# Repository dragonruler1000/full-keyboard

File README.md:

# full-keyboard
This is a 108 key keyboard that follows the ansi 104 key layout with 4 extra keys above the numpad. It has spots for two rotary encoders and a oled but to start i am going to not include those to reduce cost.

I wanted to make this to allow me to try a mechanical keyboard without needing to spend $200+ for a lowend mechanical keyboard and to give a chance to use QMK firmware.

To make this keyboard for your self upload the gerbers in [/PCB](/PCB) to your prefered pcb site. the case is split into 2 parts the files are in [/CAD](/CAD). firmware is built like any qmk firmware. instructions are in the folder as well. other parts are listed below and in BOM.csv and BOM.ods

Fully soldered keyboard (just need to get the case and keycaps).

BOM:
| Item Count | item name                    | Unit price $ | Total Price* | Price with discounts* | Link                                                            | Running total $* | Running total with coupons*    | part number | Notes                                                             |
|------------|------------------------------|--------------|--------------|-----------------------|-----------------------------------------------------------------|------------------|--------------------------------|-------------|-------------------------------------------------------------------|
| 1          | Raspi pico                   | 5            | 5            | 5                     | https://www.adafruit.com/product/5525                           | 5.3              | 5.3                            | 1           |                                                                   |
| 110        | 1N4148-t50A diode            | 0.0307       | 3.38         | 3.38                  | https://www.lcsc.com/product-detail/C895215.html                | 8.88             | 8.88                           | 2           | packs of 10                                                       |
| 108        | keycaps                      | 0            | 0            | 0                     | https://www.printables.com/model/118708-simple-cherry-mx-keycap | 8.88             | 8.88                           | 3           | 1g each can print myself                                          |
| 1          | Outemu(Gaote) Blue Switches  | 21.99        | 21.99        | 21.99                 | https://www.amazon.com/gp/product/B0CBSL2Z75                    | 32.19            | 32.19                          | 4           | pack of 108 price                                                 |
| 1          | DUROCK PCB mount stabalizers | 17.99        | 17.99        | 17.99                 | https://www.amazon.com/gp/product/B0B2RVN19F?psc=1              | 51.26            | 51.26                          | 5           | full set                                                          |
| 1          | heatset inserts              | 8.99         | 8.99         | 8.99                  | https://www.amazon.com/gp/product/B0CS6XJSSL                    | 60.79            | 60.79                          | 6           |                                                                   |
| 1          | PCB                          | 35.3         | 35.3         | 35.3                  | https://www.jlcpcb.com                                          | 98.21            | 98.21                          | 7           | jlcpcb price is cheaper then pcbway before shipping               |
| 1          | case                         | 0            | 0            | 0                     | N/A                                                             | 98.21            | 98.21                          | 8           | print using printing legion                                       |
| 1          | Shipping for PCB             | 41.4         | 41.4         | 22.16                 | N/A                                                             | 142.09           | 121.7                          |             | First shipping cost is for DHL express second one is for GDL      |
| 1          | digikey shipping and tarrifs | 5.36         | 5.36         | 5.36                  | N/A                                                             | 147.77           | 127.38                         |             | ±$5                                                               |
| 1          | Adafruit shipping            | 5.72         | 5.72         | 5.72                  | N/A                                                             | 153.83           | 133.44                         |             |                                                                   |
| 1          | amazon shipping              | 0            | 0            | 0                     | N/A                                                             | 153.83           | 133.44                         |             | over min amount for free shipping/have a 30 trial of amazon prime |
|            |                              |              |              |                       |                                                                 |                  |                                |             |                                                                   |
|            |                              |              |              |                       |                                                                 |                  | *Rounded to two decimal places |             |                                                                   |

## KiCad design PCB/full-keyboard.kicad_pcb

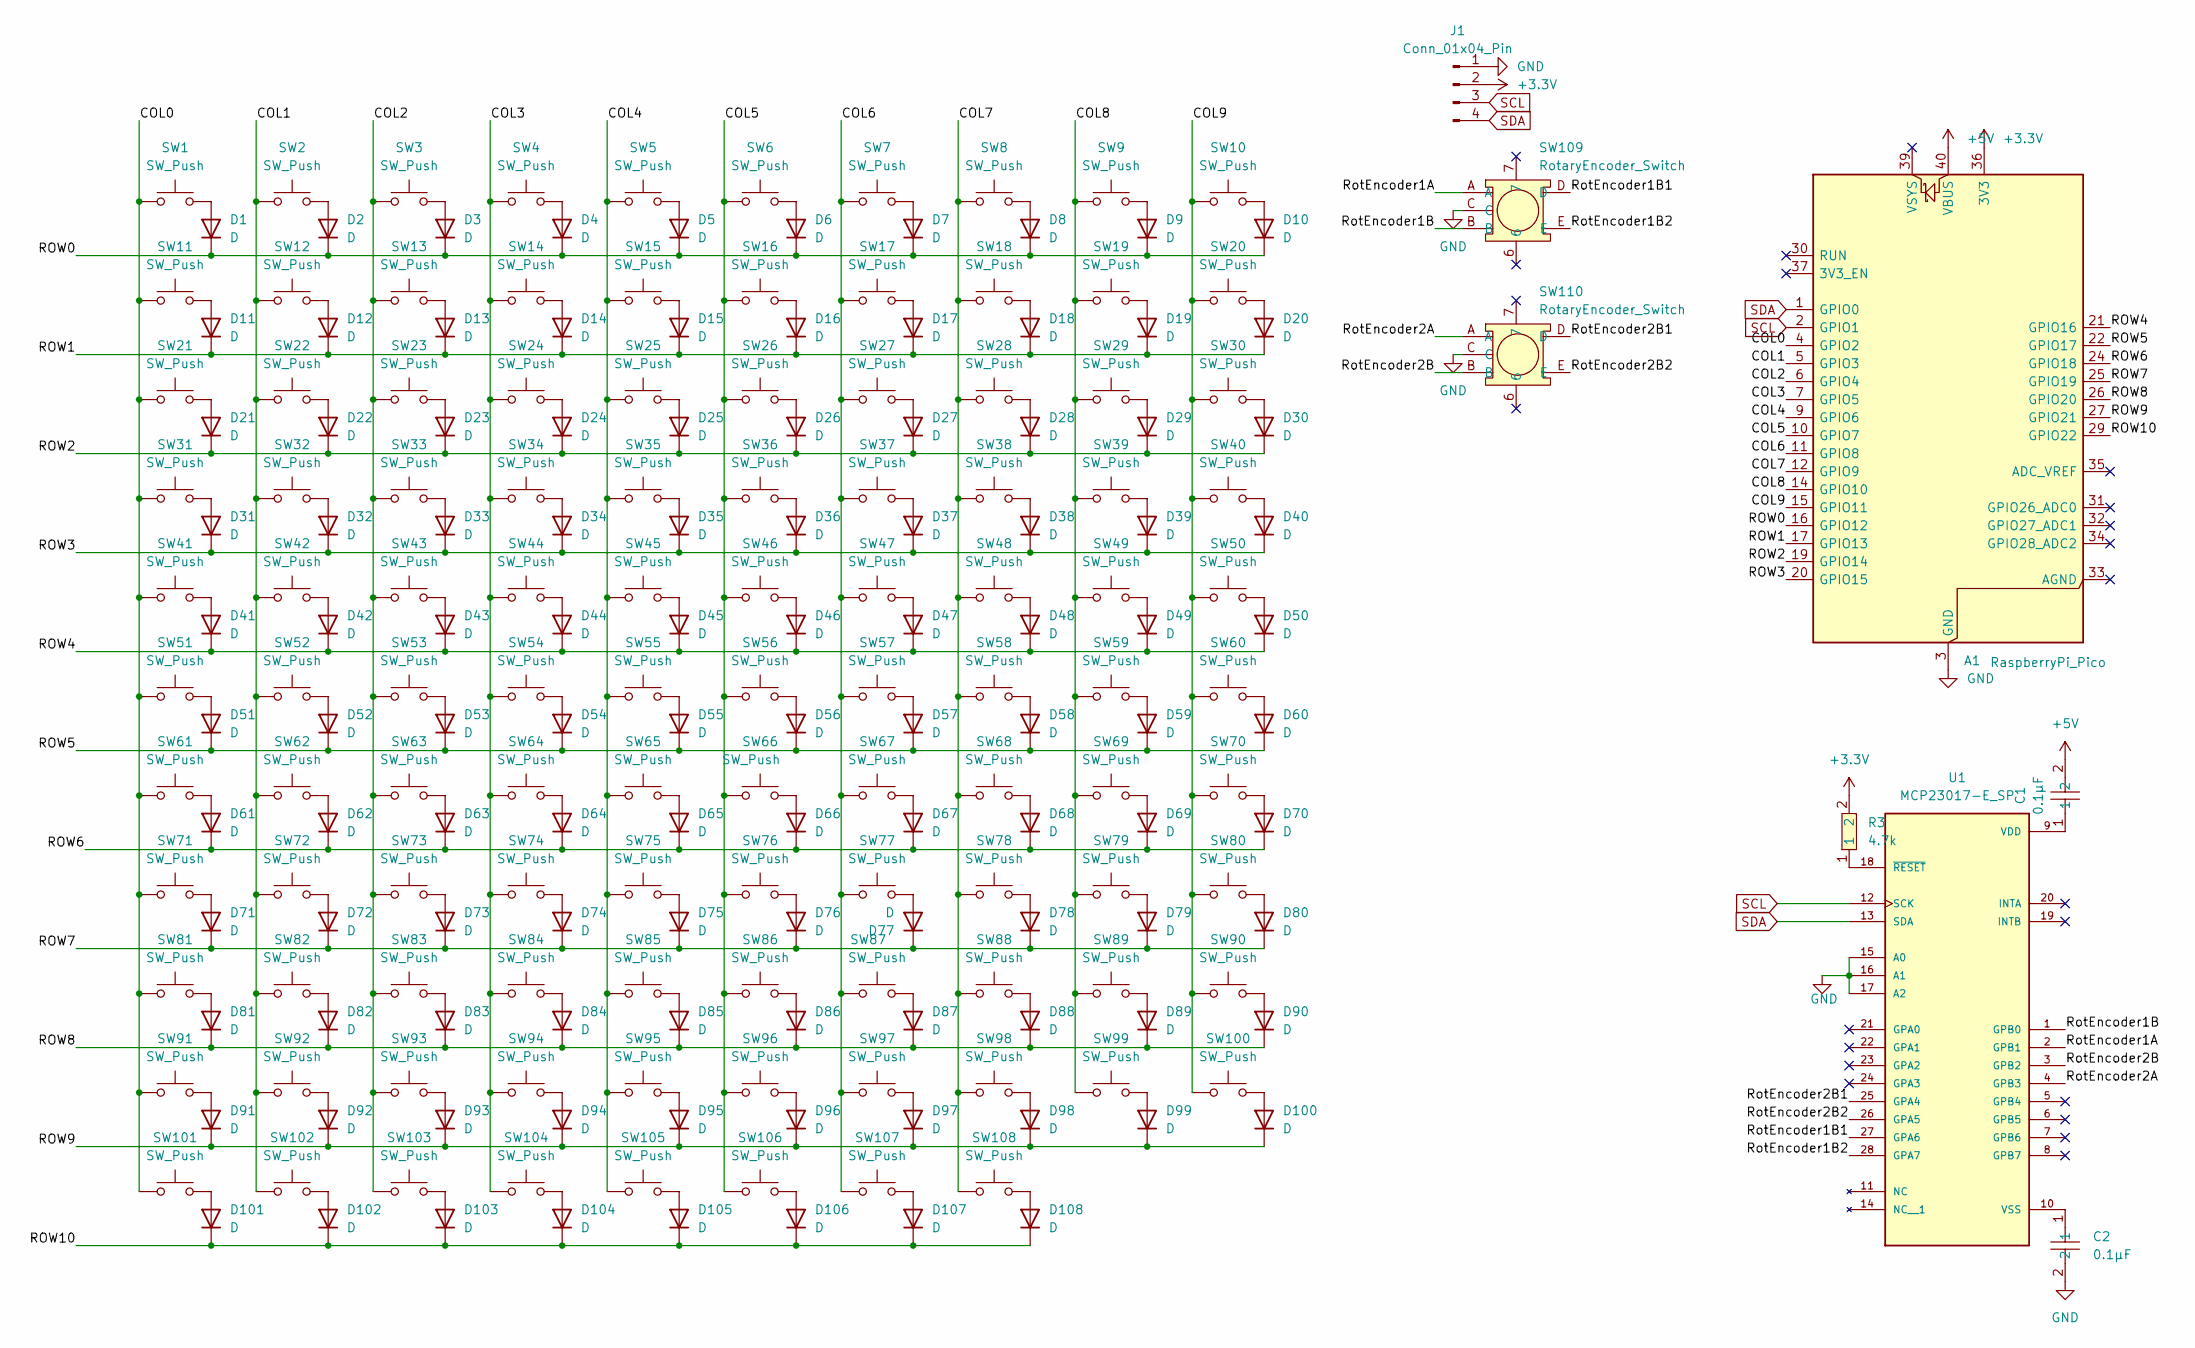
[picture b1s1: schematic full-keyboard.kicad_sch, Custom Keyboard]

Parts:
A1: RaspberryPi_Pico; RaspberryPi_Pico_Common_THT
C1, C2: 0.1µF; CAP-TH_L5.1-W3.2-P5.08-D0.50; LCSC Part C1622885
D1, D2, D3, D4, D5, D6, D7, D8, D9, D10, D11, D12, D13, D14, D15, D16, D17, D18, D19, D20, D21, D22, D23, D24, D25, D26, D27, D28, D29, D30, D31, D32, D33, D34, D35, D36, D37, D38, D39, D40, D41, D42, D43, D44, D45, D46, D47, D48, D49, D50, D51, D52, D53, D54, D55, D56, D57, D58, D59, D60, D61, D62, D63, D64, D65, D66, D67, D68, D69, D70, D71, D72, D73, D74, D75, D76, D77, D78, D79, D80, D81, D82, D83, D84, D85, D86, D87, D88, D89, D90, D91, D92, D93, D94, D95, D96, D97, D98, D99, D100, D101, D102, D103, D104, D105, D106, D107, D108: D; D_DO-35_SOD27_P7.62mm_Horizontal
J1: Conn_01x04_Pin; SSD1306-0.91-OLED-4pin-128x32
R3: 4.7k; RES-TH_BD2.5-L4.7-P8.70-D0.5; LCSC Part C172560
SW1, SW2, SW3, SW4, SW5, SW6, SW7, SW8, SW9, SW10, SW11, SW12, SW13, SW14, SW15, SW16, SW17, SW18, SW19, SW20, SW21, SW22, SW23, SW24, SW25, SW26, SW27, SW28, SW29, SW30, SW31, SW32, SW33, SW35, SW36, SW37, SW38, SW39, SW40, SW41, SW43, SW44, SW45, SW46, SW47, SW48, SW49, SW50, SW51, SW52, SW53, SW54, SW56, SW57, SW58, SW59, SW60, SW61, SW64, SW65, SW66, SW67, SW68, SW69, SW70, SW71, SW72, SW73, SW74, SW76, SW77, SW78, SW80, SW81, SW82, SW83, SW84, SW85, SW86, SW87, SW88, SW89, SW91, SW92, SW93, SW94, SW104, SW105, SW106, SW108: SW_Push; SW_Hotswap_Kailh_MX_1.00u
SW34, SW107: SW_Push; SW_Hotswap_Kailh_MX_2.00u
SW42, SW55: SW_Push; SW_Hotswap_Kailh_MX_1.50u
SW62, SW95: SW_Push; SW_Hotswap_Kailh_MX_2.00u_90deg
SW63: SW_Push; SW_Hotswap_Kailh_MX_1.75u
SW75, SW79: SW_Push; SW_Hotswap_Kailh_MX_2.25u
SW90: SW_Push; SW_Hotswap_Kailh_MX_2.75u
SW96, SW97, SW98, SW100, SW101, SW102, SW103: SW_Push; SW_Hotswap_Kailh_MX_1.25u
SW99: SW_Push; SW_Hotswap_Kailh_MX_6.25u
SW109, SW110: RotaryEncoder_Switch; SW-TH_EC11XXXXXXXX; LCSC Part C470754
U1: MCP23017-E_SP; DIP-28_W7.62mm; PARTREV D

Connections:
+3.3V: A1.36 (3V3), J1.2, R3.2
+5V: A1.40 (VBUS), C1.2
/COL0: A1.4 (GPIO2), SW1.1, SW11.1, SW21.1, SW31.1, SW41.1, SW51.1, SW61.1, SW71.1, SW81.1, SW91.1, SW101.1
/COL1: A1.5 (GPIO3), SW2.1, SW12.1, SW22.1, SW32.1, SW42.1, SW52.1, SW62.1, SW72.1, SW82.1, SW92.1, SW102.1
/COL2: A1.6 (GPIO4), SW3.1, SW13.1, SW23.1, SW33.1, SW43.1, SW53.1, SW63.1, SW73.1, SW83.1, SW93.1, SW103.1
/COL3: A1.7 (GPIO5), SW4.1, SW14.1, SW24.1, SW34.1, SW44.1, SW54.1, SW64.1, SW74.1, SW84.1, SW94.1, SW104.1
/COL4: A1.9 (GPIO6), SW5.1, SW15.1, SW25.1, SW35.1, SW45.1, SW55.1, SW65.1, SW75.1, SW85.1, SW95.1, SW105.1
/COL5: A1.10 (GPIO7), SW6.1, SW16.1, SW26.1, SW36.1, SW46.1, SW56.1, SW66.1, SW76.1, SW86.1, SW96.1, SW106.1
/COL6: A1.11 (GPIO8), SW7.1, SW17.1, SW27.1, SW37.1, SW47.1, SW57.1, SW67.1, SW77.1, SW87.1, SW97.1, SW107.1
/COL7: A1.12 (GPIO9), SW8.1, SW18.1, SW28.1, SW38.1, SW48.1, SW58.1, SW68.1, SW78.1, SW88.1, SW98.1, SW108.1
/COL8: A1.14 (GPIO10), SW9.1, SW19.1, SW29.1, SW39.1, SW49.1, SW59.1, SW69.1, SW79.1, SW89.1, SW99.1
/COL9: A1.15 (GPIO11), SW10.1, SW20.1, SW30.1, SW40.1, SW50.1, SW60.1, SW70.1, SW80.1, SW90.1, SW100.1
/ROW0: A1.16 (GPIO12), D1.1 (K), D2.1 (K), D3.1 (K), D4.1 (K), D5.1 (K), D6.1 (K), D7.1 (K), D8.1 (K), D9.1 (K), D10.1 (K)
/ROW1: A1.17 (GPIO13), D11.1 (K), D12.1 (K), D13.1 (K), D14.1 (K), D15.1 (K), D16.1 (K), D17.1 (K), D18.1 (K), D19.1 (K), D20.1 (K)
/ROW2: A1.19 (GPIO14), D21.1 (K), D22.1 (K), D23.1 (K), D24.1 (K), D25.1 (K), D26.1 (K), D27.1 (K), D28.1 (K), D29.1 (K), D30.1 (K)
/ROW3: A1.20 (GPIO15), D31.1 (K), D32.1 (K), D33.1 (K), D34.1 (K), D35.1 (K), D36.1 (K), D37.1 (K), D38.1 (K), D39.1 (K), D40.1 (K)
/ROW4: A1.21 (GPIO16), D41.1 (K), D42.1 (K), D43.1 (K), D44.1 (K), D45.1 (K), D46.1 (K), D47.1 (K), D48.1 (K), D49.1 (K), D50.1 (K)
/ROW5: A1.22 (GPIO17), D51.1 (K), D52.1 (K), D53.1 (K), D54.1 (K), D55.1 (K), D56.1 (K), D57.1 (K), D58.1 (K), D59.1 (K), D60.1 (K)
/ROW6: A1.24 (GPIO18), D61.1 (K), D62.1 (K), D63.1 (K), D64.1 (K), D65.1 (K), D66.1 (K), D67.1 (K), D68.1 (K), D69.1 (K), D70.1 (K)
/ROW7: A1.25 (GPIO19), D71.1 (K), D72.1 (K), D73.1 (K), D74.1 (K), D75.1 (K), D76.1 (K), D77.1 (K), D78.1 (K), D79.1 (K), D80.1 (K)
/ROW8: A1.26 (GPIO20), D81.1 (K), D82.1 (K), D83.1 (K), D84.1 (K), D85.1 (K), D86.1 (K), D87.1 (K), D88.1 (K), D89.1 (K), D90.1 (K)
/ROW9: A1.27 (GPIO21), D91.1 (K), D92.1 (K), D93.1 (K), D94.1 (K), D95.1 (K), D96.1 (K), D97.1 (K), D98.1 (K), D99.1 (K), D100.1 (K)
/ROW10: A1.29 (GPIO22), D101.1 (K), D102.1 (K), D103.1 (K), D104.1 (K), D105.1 (K), D106.1 (K), D107.1 (K), D108.1 (K)
/RotEncoder1A: SW109.A, U1.2 (GPB1)
/RotEncoder1B: SW109.B, U1.1 (GPB0)
/RotEncoder1B1: SW109.D, U1.27 (GPA6)
/RotEncoder1B2: SW109.E, U1.28 (GPA7)
/RotEncoder2A: SW110.A, U1.4 (GPB3)
/RotEncoder2B: SW110.B, U1.3 (GPB2)
/RotEncoder2B1: SW110.D, U1.25 (GPA4)
/RotEncoder2B2: SW110.E, U1.26 (GPA5)
GND: A1.3 (GND), A1.8 (GND), A1.13 (GND), A1.18 (GND), A1.23 (GND), A1.28 (GND), A1.38 (GND), C2.2, J1.1, SW109.C, SW110.C, U1.15 (A0), U1.16 (A1), U1.17 (A2)
unnamed: D1.2 (A), SW1.2
unnamed: D2.2 (A), SW2.2
unnamed: D3.2 (A), SW3.2
unnamed: D4.2 (A), SW4.2
unnamed: D5.2 (A), SW5.2
unnamed: D6.2 (A), SW6.2
unnamed: D7.2 (A), SW7.2
unnamed: D8.2 (A), SW8.2
unnamed: D9.2 (A), SW9.2
unnamed: D10.2 (A), SW10.2
unnamed: D11.2 (A), SW11.2
unnamed: D12.2 (A), SW12.2
unnamed: D13.2 (A), SW13.2
unnamed: D14.2 (A), SW14.2
unnamed: D15.2 (A), SW15.2
unnamed: D16.2 (A), SW16.2
unnamed: D17.2 (A), SW17.2
unnamed: D18.2 (A), SW18.2
unnamed: D19.2 (A), SW19.2
unnamed: D20.2 (A), SW20.2
unnamed: D21.2 (A), SW21.2
unnamed: D22.2 (A), SW22.2
unnamed: D23.2 (A), SW23.2
unnamed: D24.2 (A), SW24.2
unnamed: D25.2 (A), SW25.2
unnamed: D26.2 (A), SW26.2
unnamed: D27.2 (A), SW27.2
unnamed: D28.2 (A), SW28.2
unnamed: D29.2 (A), SW29.2
unnamed: D30.2 (A), SW30.2
unnamed: D31.2 (A), SW31.2
unnamed: D32.2 (A), SW32.2
unnamed: D33.2 (A), SW33.2
unnamed: D34.2 (A), SW34.2
unnamed: D35.2 (A), SW35.2
unnamed: D36.2 (A), SW36.2
unnamed: D37.2 (A), SW37.2
unnamed: D38.2 (A), SW38.2
unnamed: D39.2 (A), SW39.2
unnamed: D40.2 (A), SW40.2
unnamed: D41.2 (A), SW41.2
unnamed: D42.2 (A), SW42.2
unnamed: D43.2 (A), SW43.2
unnamed: D44.2 (A), SW44.2
unnamed: D45.2 (A), SW45.2
unnamed: D46.2 (A), SW46.2
unnamed: D47.2 (A), SW47.2
unnamed: D48.2 (A), SW48.2
unnamed: D49.2 (A), SW49.2
unnamed: D50.2 (A), SW50.2
unnamed: D51.2 (A), SW51.2
unnamed: D52.2 (A), SW52.2
unnamed: D53.2 (A), SW53.2
unnamed: D54.2 (A), SW54.2
unnamed: D55.2 (A), SW55.2
unnamed: D56.2 (A), SW56.2
unnamed: D57.2 (A), SW57.2
unnamed: D58.2 (A), SW58.2
unnamed: D59.2 (A), SW59.2
unnamed: D60.2 (A), SW60.2
unnamed: D61.2 (A), SW61.2
unnamed: D62.2 (A), SW62.2
unnamed: D63.2 (A), SW63.2
unnamed: D64.2 (A), SW64.2
unnamed: D65.2 (A), SW65.2
unnamed: D66.2 (A), SW66.2
unnamed: D67.2 (A), SW67.2
unnamed: D68.2 (A), SW68.2
unnamed: D69.2 (A), SW69.2
unnamed: D70.2 (A), SW70.2
unnamed: D71.2 (A), SW71.2
unnamed: D72.2 (A), SW72.2
unnamed: D73.2 (A), SW73.2
unnamed: D74.2 (A), SW74.2
unnamed: D75.2 (A), SW75.2
unnamed: D76.2 (A), SW76.2
unnamed: D77.2 (A), SW77.2
unnamed: D78.2 (A), SW78.2
unnamed: D79.2 (A), SW79.2
unnamed: D80.2 (A), SW80.2
unnamed: D81.2 (A), SW81.2
unnamed: D82.2 (A), SW82.2
unnamed: D83.2 (A), SW83.2
unnamed: D84.2 (A), SW84.2
unnamed: D85.2 (A), SW85.2
unnamed: D86.2 (A), SW86.2
unnamed: D87.2 (A), SW87.2
unnamed: D88.2 (A), SW88.2
unnamed: D89.2 (A), SW89.2
unnamed: D90.2 (A), SW90.2
unnamed: D91.2 (A), SW91.2
unnamed: D92.2 (A), SW92.2
unnamed: D93.2 (A), SW93.2
unnamed: D94.2 (A), SW94.2
unnamed: D95.2 (A), SW95.2
unnamed: D96.2 (A), SW96.2
unnamed: D97.2 (A), SW97.2
unnamed: D98.2 (A), SW98.2
unnamed: D99.2 (A), SW99.2
unnamed: D100.2 (A), SW100.2
unnamed: D101.2 (A), SW101.2
unnamed: D102.2 (A), SW102.2
unnamed: D103.2 (A), SW103.2
unnamed: D104.2 (A), SW104.2
unnamed: D105.2 (A), SW105.2
unnamed: D106.2 (A), SW106.2
unnamed: D107.2 (A), SW107.2
unnamed: D108.2 (A), SW108.2
unnamed: C1.1, U1.9 (VDD)
unnamed: C2.1, U1.10 (VSS)
unnamed: R3.1, U1.18 (~RESET)
SCL: A1.2 (GPIO1), J1.3, U1.12 (SCK)
SDA: A1.1 (GPIO0), J1.4, U1.13 (SDA)

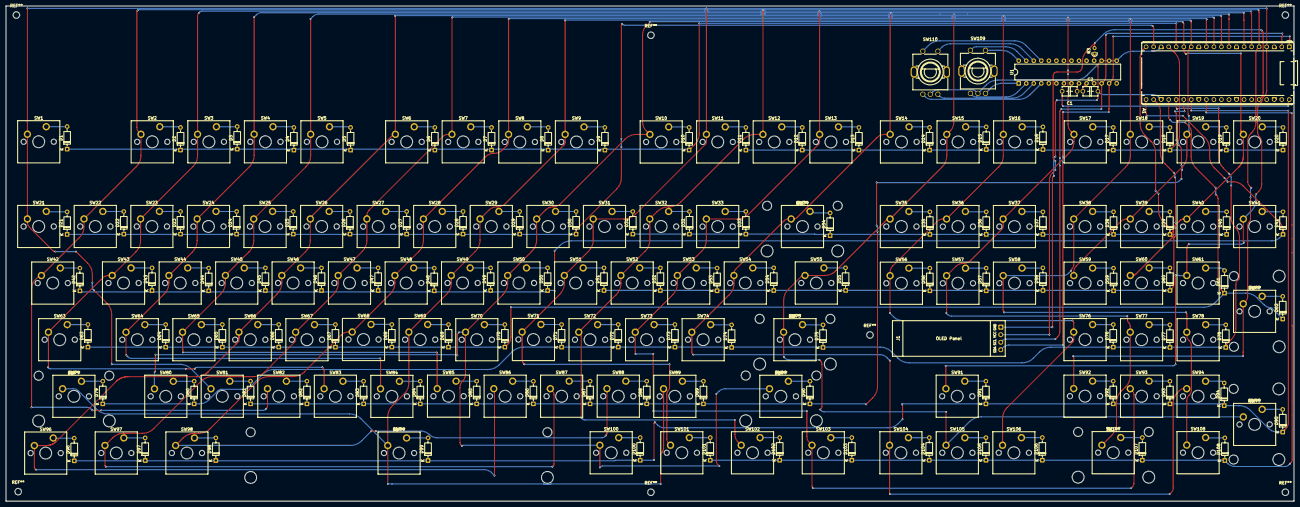
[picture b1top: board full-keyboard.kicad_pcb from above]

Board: 2 copper layers, 434.0 x 166.8 mm, 224 parts (0 on the bottom side), 145 nets.

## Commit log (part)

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2025-11-09 Start work on the keyboard
2025-11-09 Started laying out the schematic and found the library for the switches i am going to use.
2025-11-10 started work on the schematic. got all the switches layed out
2025-12-05 added BOM and added the leds to the schematic
2025-12-05 resetting the submodules
2025-12-05 trying to add BOM and readded the keyswitch submodule
2025-12-05 added the BOM
2025-12-05 changed switches and added encoders to the BOM
2025-12-05 updated some footprints and found a cheaper hotswap socket kit
2025-12-06 worked on laying out the keyboard
2025-12-06 started laying out the pcb
2025-12-06 moved some keys on the matrix
    re adjusting the keys on the matrix so they match there position on the keyboard.
2025-12-07 set the layout in the schematic to match the pcb layout for the keys
2025-12-08 changed the key matrix and started swapping keyswith libraries
2025-12-09 macking sure changes where backed up.
2025-12-09 finnished placing the keyswitches properly and started working on placing the leds
2025-12-12 got the leds placed into position
2025-12-21 changeing to SparkFun Pro Micro - RP2040 and adding LEDs to the BOM
2025-12-25 added the stabalizers for the 2u+ keys
2025-12-25 swaped to using the footprint provided by easyeda2kicad for the pull up resister
2025-12-29 switching to non lfs files, hopefully
2025-12-30 hopefully removed gitlfs tracking
2026-01-05 switching to a new repo to fix git lfs problems
2026-01-05 add git ignore and manulay update JOURNAL becasue i can
2026-01-05 added correct JOURNAL
2026-01-07 added case model
2026-01-08 added QMK firmware
2026-01-08 add images and BOM to readme
2026-01-08 updated bom to use parts from digikey for cheaper overall cost
2026-01-17 update BOM to use cheaper parts from aliexpress
2026-01-17 update item names
2026-02-18 Revise BOM with updated item information
    Updated BOM with new item details and prices.
2026-02-18 added cart images and updated bom to match current prices
2026-02-22 switched to case made by TurboCase for a nicer case with standoff.
2026-03-07 made the case in FreeCAD and moved the locations of two of the mounting holes and added a 7th
2026-03-07 added stl files to git lfs
2026-03-07 i don't know what i'm doing
2026-03-07 removed file that i dont need to include
2026-03-07 teying stuff
2026-03-07 fixed?
2026-03-07 \updated gerbers
2026-03-07 updated BOM to match current pricing of parts
2026-03-07 updated cart images and added heatset inserts to BOM
2026-04-10 Revise keyboard case details and add images
    Updated README to reflect case design changes and added images.
2026-04-21 Updated PCB to add standoff support and made a case to support the keyboard with standoffsx
2026-04-21 update CAD info in README
